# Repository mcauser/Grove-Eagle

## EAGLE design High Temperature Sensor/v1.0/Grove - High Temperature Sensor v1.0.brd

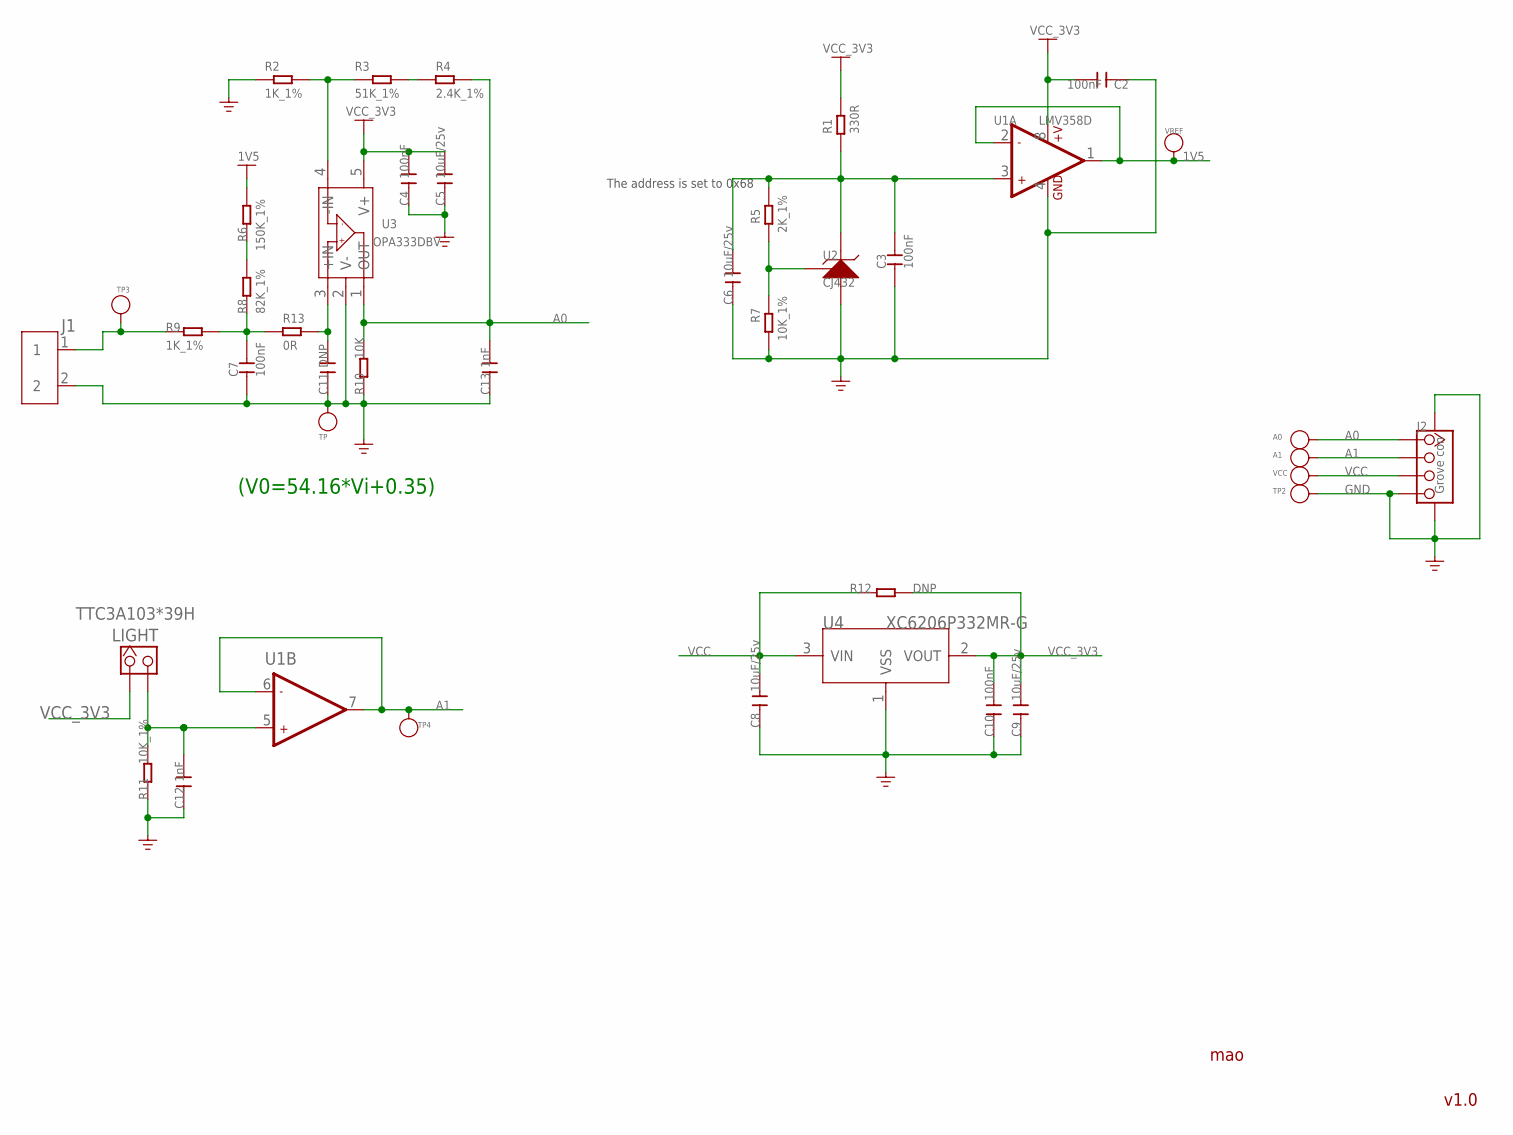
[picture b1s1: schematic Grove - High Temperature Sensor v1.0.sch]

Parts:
A0, A1: TP3; TP_4545
C2, C3, C4, C7, C10: 100nF; C0603
C5, C6, C8, C9: 10uF/25v; C0805
C11: DNP; C0603
C12, C13: 1nF; C0603
J1: SCREW-TERMINAL-2P'3.5'; 2P-3.5
J2: Grove con; 4P-SMD-2.0
LIGHT: TTC3A103*39H; CK_1*2
R1: 330R; R0603
R2, R9: 1K_1%; R0603
R3: 51K_1%; R0603
R4: 2.4K_1%; R0603
R5: 2K_1%; R0603
R6: 150K_1%; R0603
R7, R11: 10K_1%; R0603
R8: 82K_1%; R0603
R10: 10K; R0603
R12: DNP; R0603
R13: 0R; R0603
TP, TP2, TP3, TP4: PAD-TEST-POINT'4545'; TP_4545
U1: LMV358D; SO08
U2: CJ432; SOT23
U3: OPA333DBV; SOT23-5
U4: XC6206P332MR-G; SOT23
VCC: TP2; TP_4545
VREF: TP4; TP_4545

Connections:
1V5: R6.2, U1.1 (OUT1), U1.2 (-IN1), VREF.T
A0: A0.T, C13.2, J2.1, R4.1, R10.2, U3.1 (OUT)
A1: A1.T, J2.2, TP4.T, U1.6 (-IN2), U1.7 (OUT2)
GND: C2.1, C3.1, C4.1, C5.1, C6.1, C7.1, C8.1, C9.1, C10.1, C11.1, C12.1, C13.1, J1.2, J2.4, J2.SS1, J2.SS2, R2.2, R7.2, R10.1, R11.1, TP.T, TP2.T, U1.4 (GND), U2.3 (A), U3.2 (V-), U4.1 (VSS)
unnamed: C7.2, R8.1, R9.2, R13.2
unnamed: R2.1, R3.2, U3.4 (-IN)
unnamed: J1.1, R9.1, TP3.T
unnamed: R3.1, R4.2
unnamed: C12.2, LIGHT.2, R11.2, U1.5 (+IN2)
unnamed: R6.1, R8.2
unnamed: C11.2, R13.1, U3.3 (+IN)
unnamed: R5.2, R7.1, U2.1 (R)
VCC: C8.2, J2.3, R12.1, U4.3 (VIN), VCC.T
VCC_3V3: C2.2, C4.2, C5.2, C9.2, C10.2, LIGHT.1, R1.1, R12.2, U1.8 (+V), U3.5 (V+), U4.2 (VOUT)
VREF: C3.2, C6.2, R1.2, R5.1, U1.3 (+IN1), U2.2 (K)

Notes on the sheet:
mao
v1.0
The address is set to 0x68
(V0=54.16*Vi+0.35)

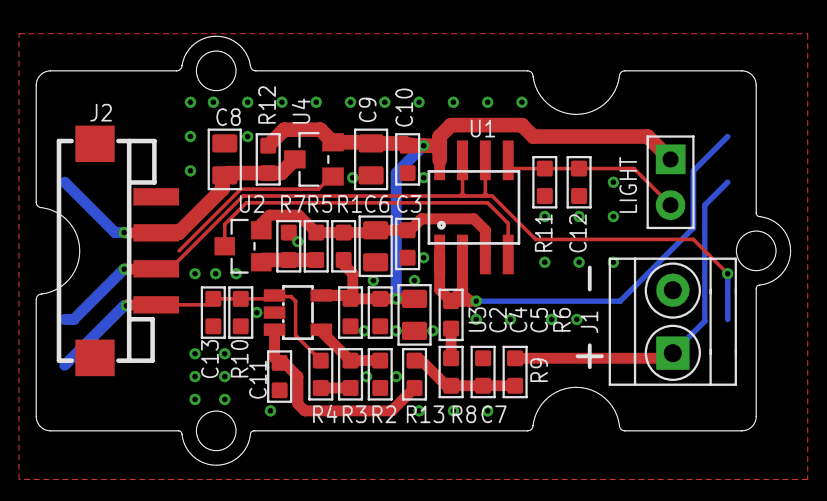
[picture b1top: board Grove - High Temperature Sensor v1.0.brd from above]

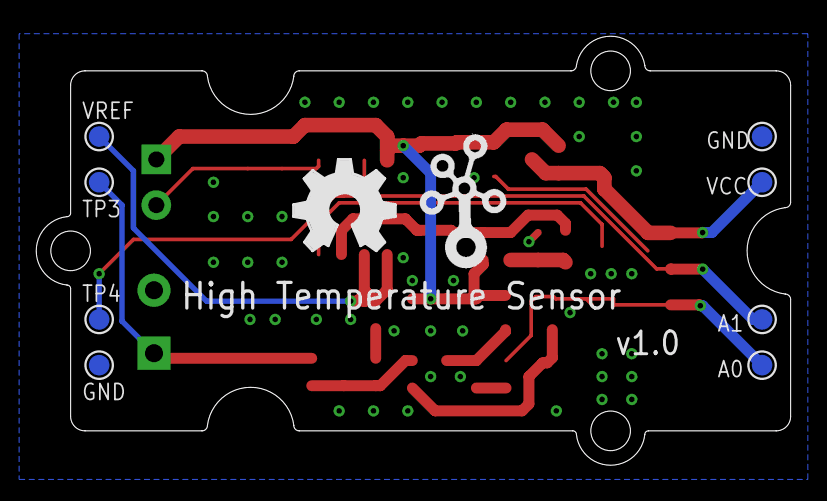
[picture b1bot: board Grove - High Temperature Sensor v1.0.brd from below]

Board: 2 copper layers, 41.9 x 23.8 mm, 43 parts (10 on the bottom side), 15 nets.

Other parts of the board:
U$9: GROVE-2CONNECTOR-SMD
U$11: TWIGLOGO
U$12: OSHW_FILLX200_NOTEXT

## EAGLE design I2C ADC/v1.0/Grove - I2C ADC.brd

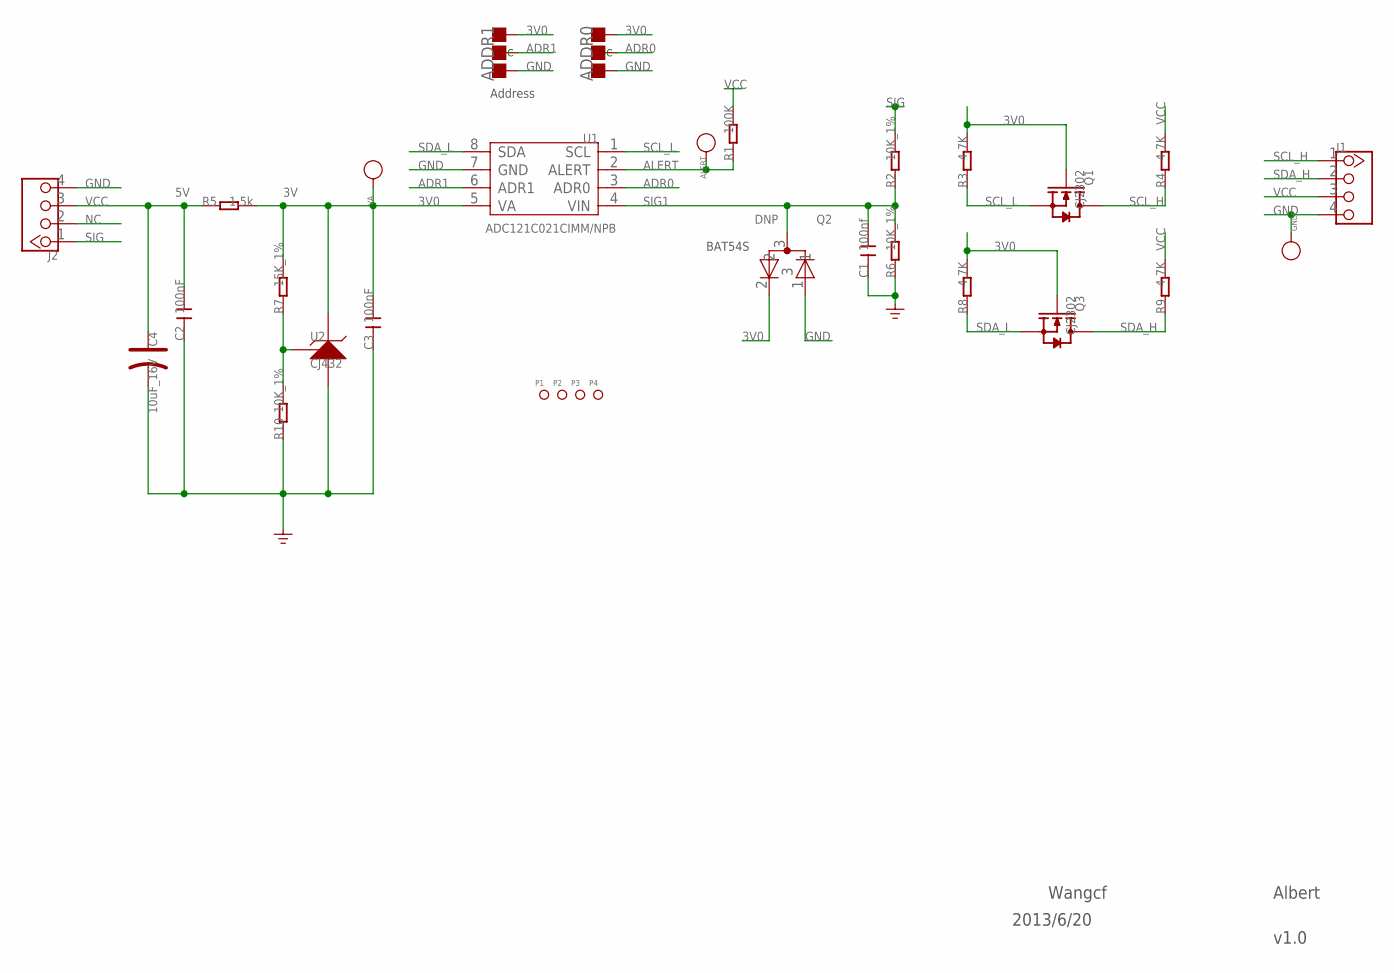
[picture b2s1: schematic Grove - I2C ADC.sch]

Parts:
ADDR0, ADDR1: DNP; 3P-SMD-4.1X1.5
ALERT: DNP; TP_3535; PARTNO DNP
C1: 100nf; C0603
C2, C3: 100nF; C0603
C4: 10uF_16V; AVX-A
GND: DNP; TP_3535
J1, J2: TWIG-4P-2.0-2.0; 4P-2.0
P1, P2, P3, P4: PAD-MARK; ROUND-MARK-1.0
Q1, Q3: CJ2302; SOT23
Q2: DNP; SOT23
R1: 100K; R0603
R2, R6, R10: 10K_1%; R0603
R3, R4, R8, R9: 4.7K; R0603
R5: 1.5k; R0603
R7: 15K_1%; R0603
U1: ADC121C021CIMM/NPB; MSOP8
U2: CJ432; SOT23
VA: DNP; TP_3535

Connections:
3V0: ADDR0.11 (R), ADDR1.11 (R), C3.2, Q1.1 (G), Q2.2, Q3.1 (G), R3.2, R5.2, R7.2, R8.2, U1.5 (VA), U2.2 (K), VA.T
ADR0: ADDR0.MM (C), U1.3 (ADR0)
ADR1: ADDR1.MM (C), U1.6 (ADR1)
ALERT: ALERT.T, R1.1, U1.2 (ALERT)
GND: ADDR0.00 (L), ADDR1.00 (L), C1.1, C2.1, C3.1, C4.-, GND.T, J1.4, J2.4, Q2.1, R6.1, R10.1, U1.7 (GND), U2.3 (A)
unnamed: R7.1, R10.2, U2.1 (R)
NC: J2.2
SCL_H: J1.1, Q1.3 (D), R4.1
SCL_L: Q1.2 (S), R3.1, U1.1 (SCL)
SDA_H: J1.2, Q3.3 (D), R9.1
SDA_L: Q3.2 (S), R8.1, U1.8 (SDA)
SIG: J2.1, R2.2
SIG1: C1.2, Q2.3, R2.1, R6.2, U1.4 (VIN)
VCC: C2.2, C4.+, J1.3, J2.3, R4.2, R5.1, R9.2

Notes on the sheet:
Address
BAT54S
Wangcf
Albert
2013/6/20
v1.0

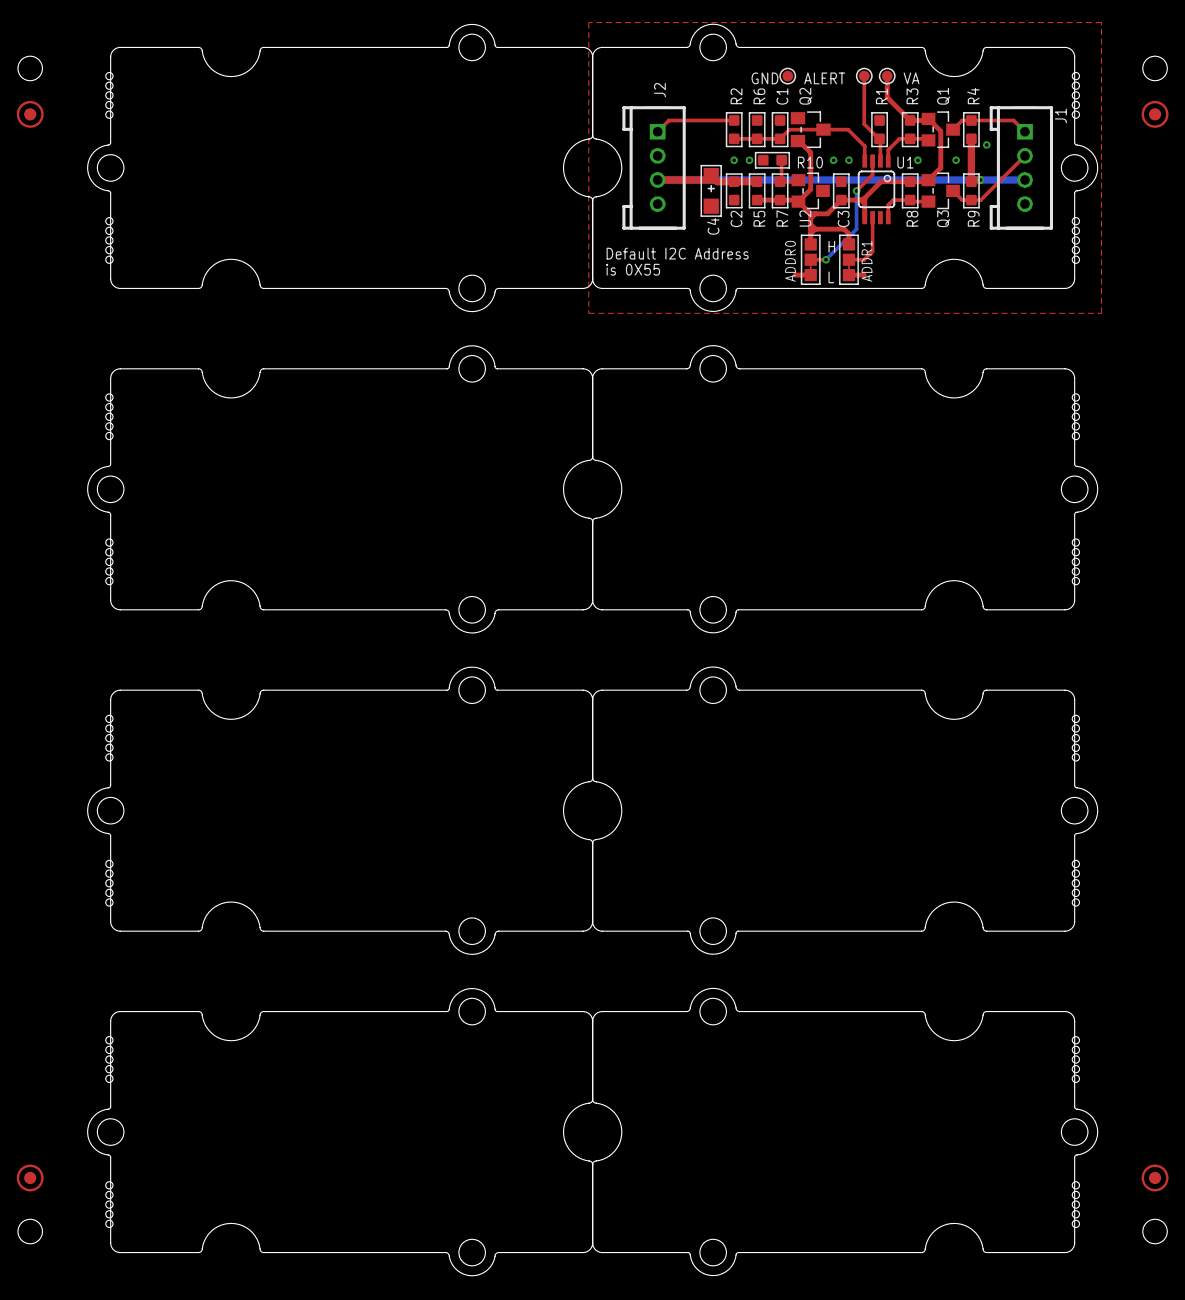
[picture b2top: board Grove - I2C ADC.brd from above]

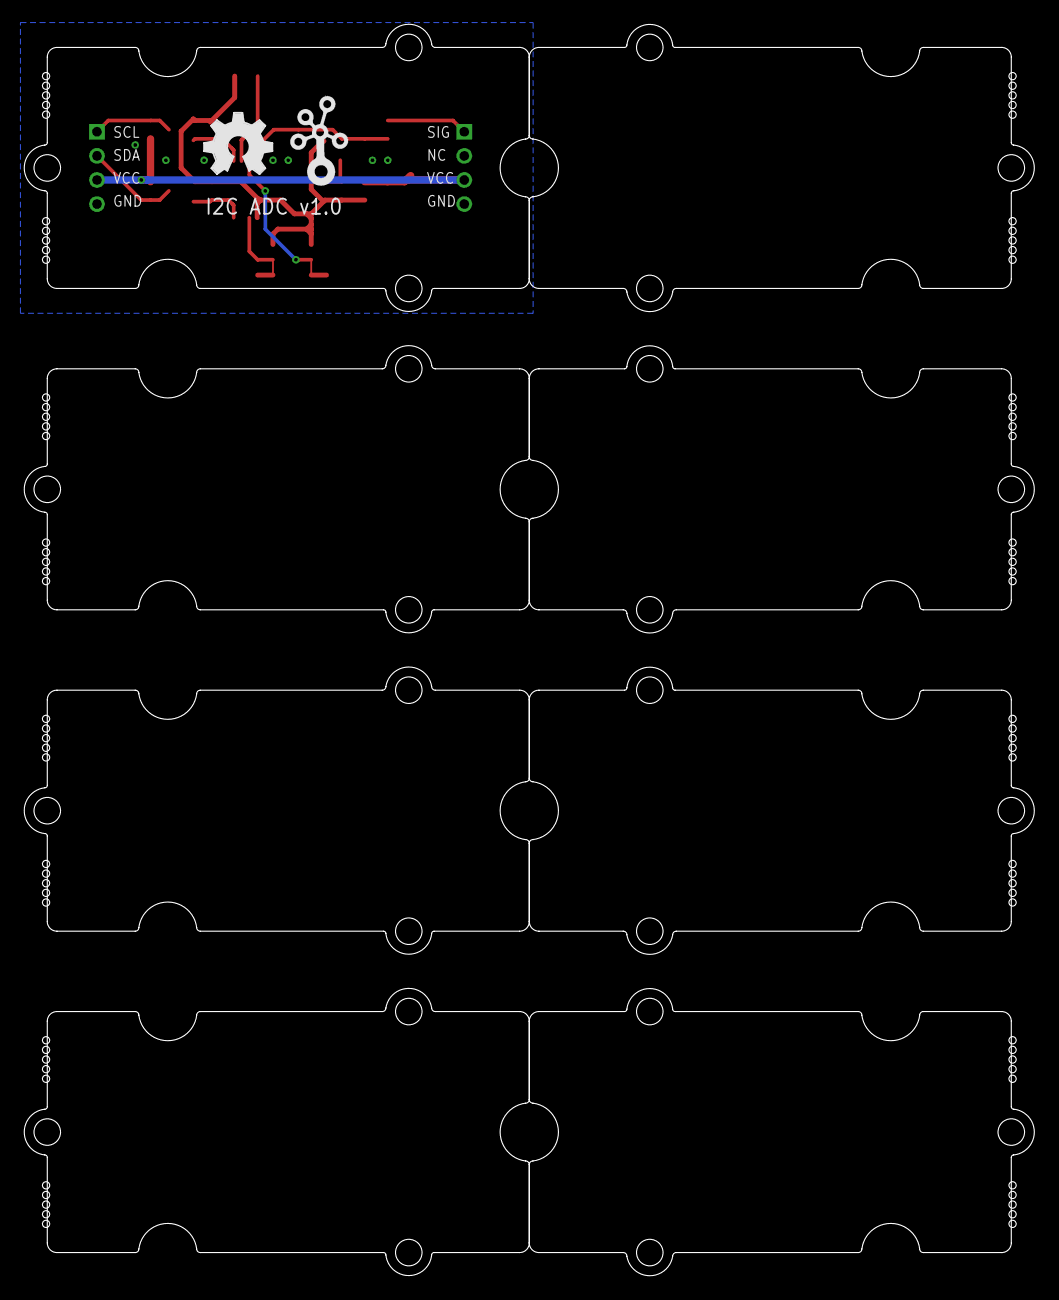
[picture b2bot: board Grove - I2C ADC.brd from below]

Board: 2 copper layers, 83.8 x 103.9 mm, 40 parts (2 on the bottom side), 13 nets.

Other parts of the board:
U$4, U$7, U$8, U$9, U$10, U$11, U$12, U$13: 2U-DIM-W/DRILL
U$5: OSHW_FILLX200_NOTEXT
U$6: TWIGLOGO

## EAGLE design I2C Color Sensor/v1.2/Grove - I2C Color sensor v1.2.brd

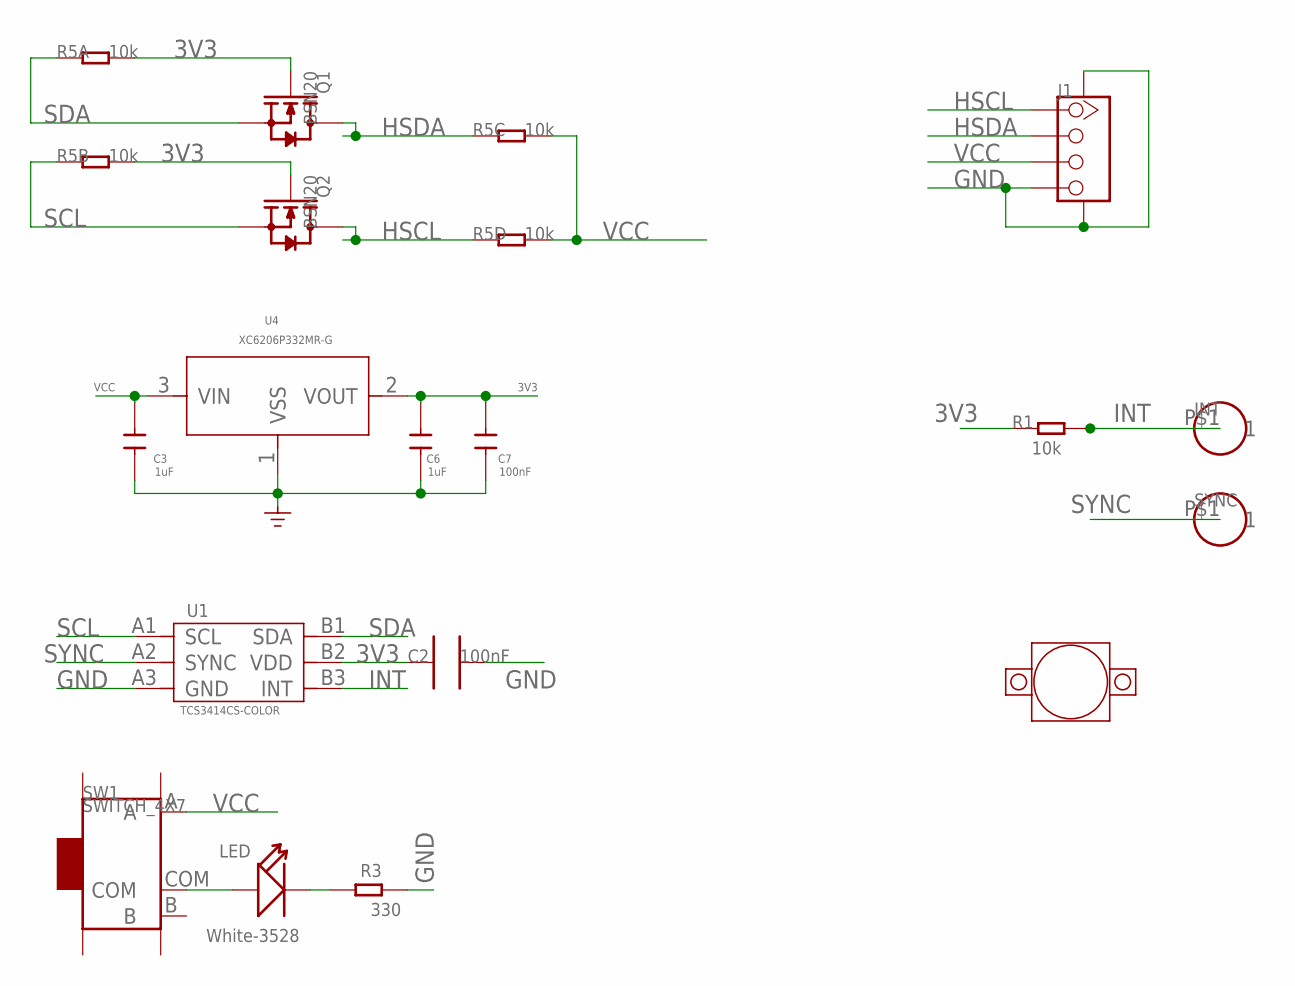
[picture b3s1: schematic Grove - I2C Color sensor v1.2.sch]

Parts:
C2: 100nF; 0603_S
C3, C6: 1uF; C0603
C7: 100nF; C0603
INT: CK_1X132; CK_1X1
J1: TWIG-4P-2.0-SMD-FEMALE-REINFORCE'DD'; 4P-SMD-2.0
LED: White-3528; LED1210
Q1, Q2: BSN20; SOT23
R1: 10k; 0603
R3: 330; 0603
R5: 10k; R1206-8
SW1: SWITCH_4X7; 4*8_SW
SYNC: CK_1X132; CK_1X1
U1: TCS3414CS-COLOR; TCS3414CS
U3: LENS_HOOD
U4: XC6206P332MR-G; SOT23

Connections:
3V3: C2.1, C6.2, C7.2, Q1.1 (G), Q2.1 (G), R1.1, R5.7 (2), R5.8 (2), U1.B2 (VDD), U4.2 (VOUT)
GND: C2.2, C3.1, C6.1, C7.1, J1.4, J1.SS1, J1.SS2, R3.1, U1.A3 (GND), U4.1 (VSS)
HSCL: J1.1, Q2.3 (D), R5.4 (1)
HSDA: J1.2, Q1.3 (D), R5.3 (1)
INT: INT.P$1, R1.2, U1.B3 (INT)
unnamed: LED.1 (+), SW1.COM
unnamed: LED.2 (-), R3.2
SCL: Q2.2 (S), R5.2 (1), U1.A1 (SCL)
SDA: Q1.2 (S), R5.1, U1.B1 (SDA)
SYNC: SYNC.P$1, U1.A2 (SYNC)
VCC: C3.2, J1.3, R5.5 (2), R5.6 (2), SW1.A, U4.3 (VIN)

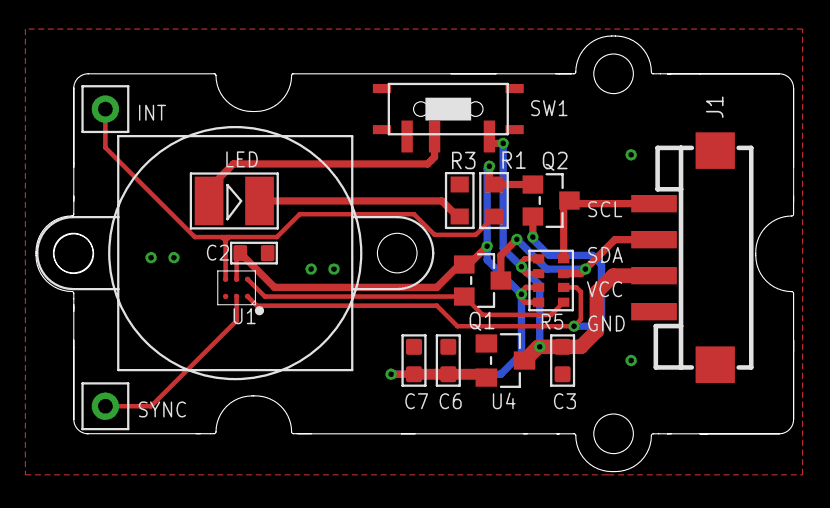
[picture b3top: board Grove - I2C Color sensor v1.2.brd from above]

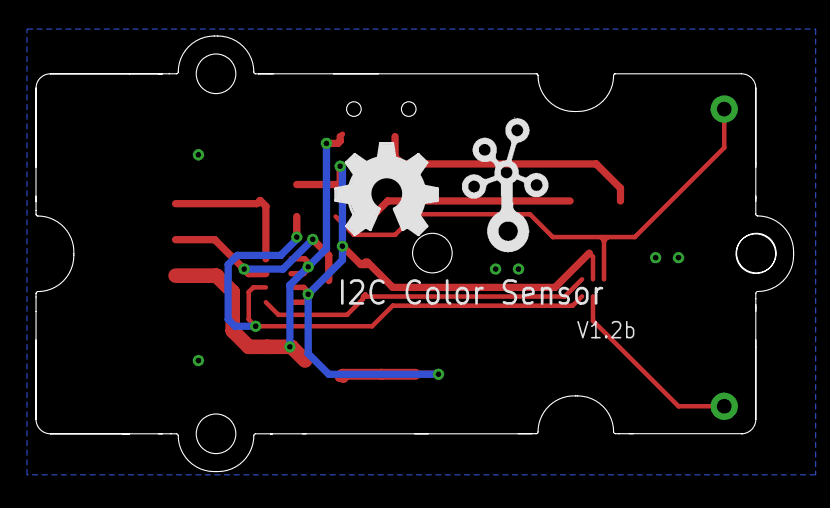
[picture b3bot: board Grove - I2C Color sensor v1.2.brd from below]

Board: 2 copper layers, 42.1 x 24.2 mm, 20 parts (2 on the bottom side), 11 nets.

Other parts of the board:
U$1: TWIGLOGO
U$2: 2U-DIM-W/-DRILL
U$3: OSHW_FILLX200_NOTEXT

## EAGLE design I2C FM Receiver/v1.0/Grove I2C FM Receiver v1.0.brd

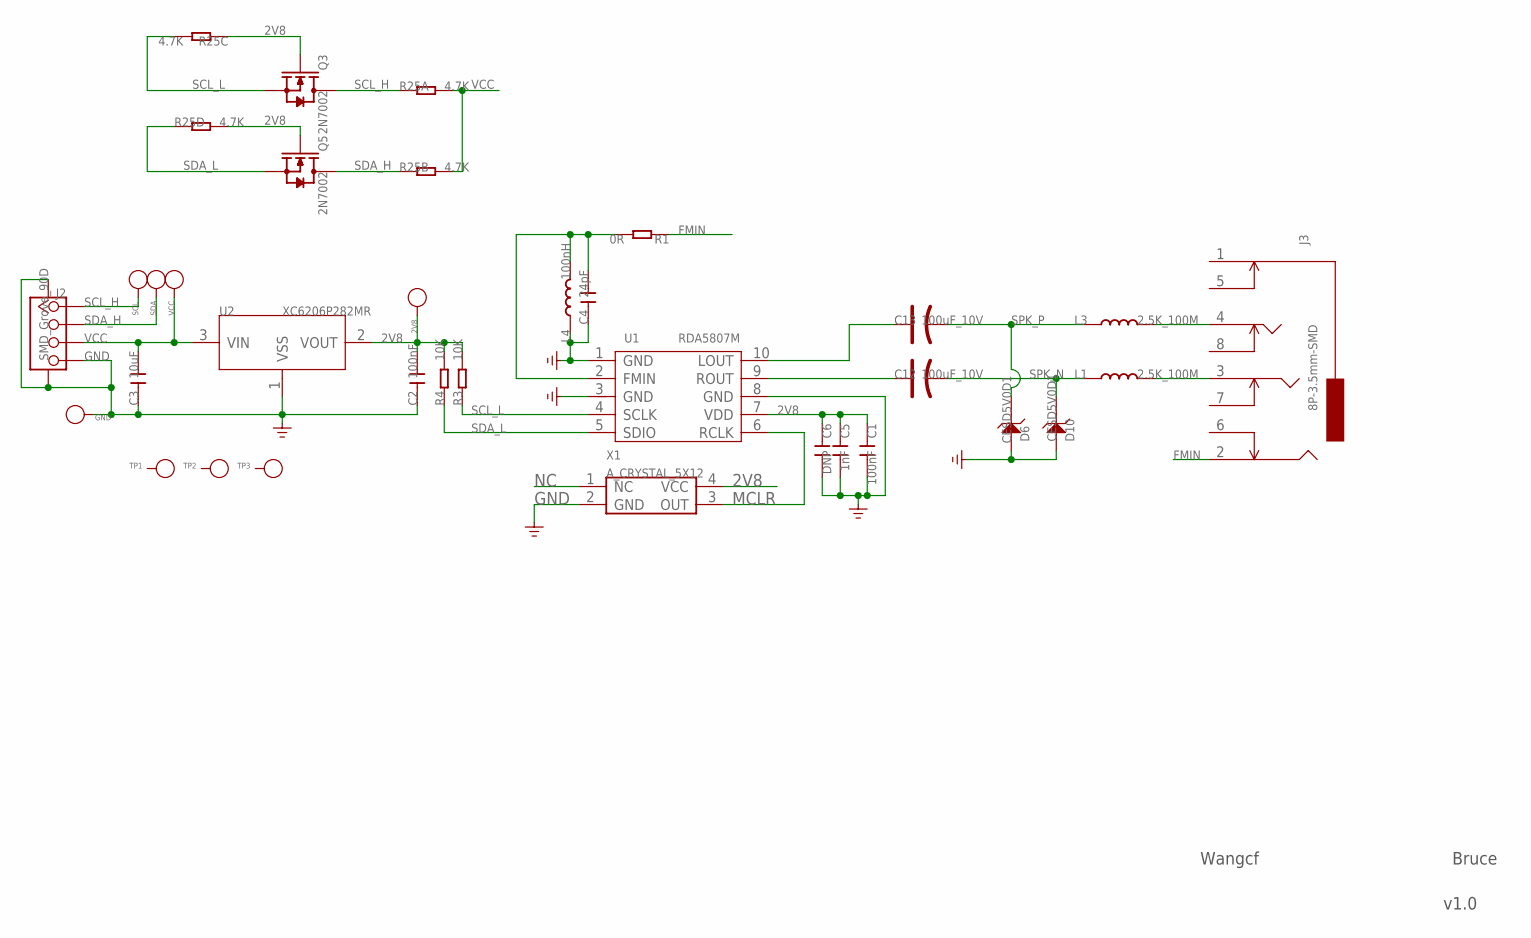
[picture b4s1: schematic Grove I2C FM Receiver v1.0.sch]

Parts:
2V8: PAD-TEST-POINT'4545'; TP_4545
C1, C2: 100nF; C0603
C3: 10uF; C0805
C4: 24pF; C0603
C5: 1nF; C0603
C6: DNP; C0603
C12, C13: 100uF_10V; AVX-B
D6, D10: CESD5V0D1; SOD123-2.7X1.6
GND: PAD-TEST-POINT'4545'; TP_4545
J2: SMD_Grove_90D; 4P-SMD-2.0
J3: 8P-3.5mm-SMD; 8P-3.5-SMD
L1, L3: 2.5K_100M; L0603
L4: 100nH; L0603
Q3, Q5: 2N7002; SOT23
R1: 0R; R0603
R3, R4: 10K; R0603
R25: 4.7K; 1206-8-3.3X2.4
SCL: PAD-TEST-POINT'4545'; TP_4545
SDA: PAD-TEST-POINT'4545'; TP_4545
TP1, TP2, TP3: PAD-TEST-POINT'4545'; TP_4545
U1: RDA5807M; MSOP10
U2: XC6206P282MR; SOT23
VCC: PAD-TEST-POINT'4545'; TP_4545
X1: A_CRYSTAL_5X12; 4P_5X12

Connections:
2V8: 2V8.T, C1.1, C2.2, C5.1, C6.1, Q3.1 (G), Q5.1 (G), R3.2, R4.2, R25.3 (1), R25.5 (2), U1.7 (VDD), U2.2 (VOUT), X1.4 (VCC)
FMIN: J3.2, R1.1
FMIN1: C4.2, L4.2, R1.2, U1.2 (FMIN)
GND: C1.2, C2.1, C3.1, C4.1, C5.2, C6.2, D6.1, D10.1, GND.T, J2.4, J2.SS1, J2.SS2, L4.1, U1.1 (GND), U1.3 (GND), U1.8 (GND), U2.1 (VSS), X1.2 (GND)
MCLR: U1.6 (RCLK), X1.3 (OUT)
unnamed: C12.+, U1.9 (ROUT)
unnamed: C13.+, U1.10 (LOUT)
unnamed: J3.4, L3.2
unnamed: J3.3, L1.2
NC: X1.1 (NC)
SCL_H: J2.1, Q3.3 (D), R25.1, SCL.T
SCL_L: Q3.2 (S), R3.1, R25.6 (2), U1.4 (SCLK)
SDA_H: J2.2, Q5.3 (D), R25.2 (1), SDA.T
SDA_L: Q5.2 (S), R4.1, R25.4 (1), U1.5 (SDIO)
SPK_N: C12.-, D10.2, L1.1
SPK_P: C13.-, D6.2, L3.1
VCC: C3.2, J2.3, R25.7 (2), R25.8 (2), U2.3 (VIN), VCC.T

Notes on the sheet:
Wangcf
Bruce
v1.0

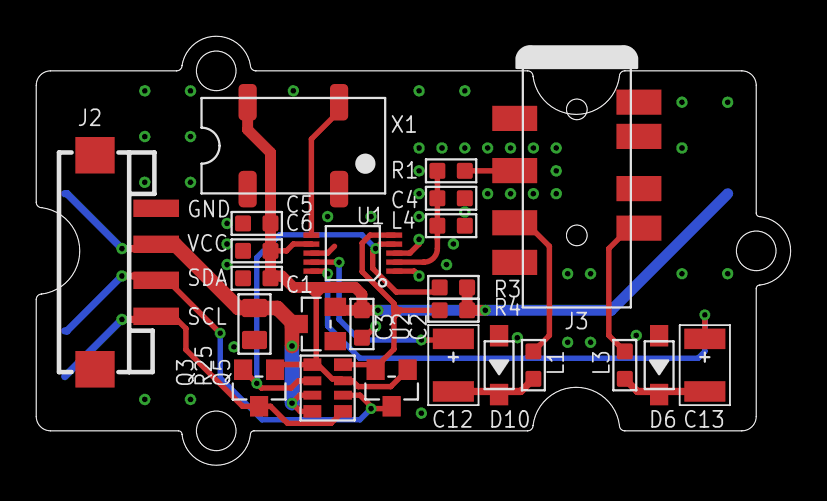
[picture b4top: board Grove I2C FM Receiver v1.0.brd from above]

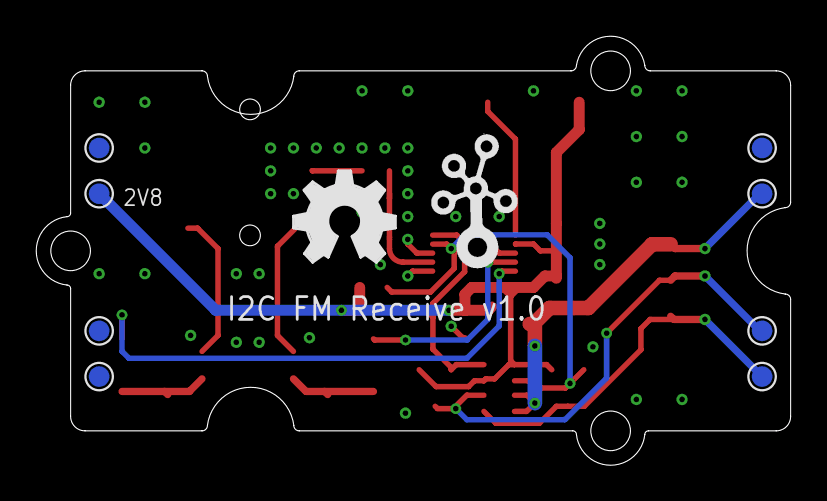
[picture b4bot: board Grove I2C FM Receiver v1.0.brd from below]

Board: 2 copper layers, 41.9 x 23.8 mm, 35 parts (10 on the bottom side), 16 nets.

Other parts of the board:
U$6: GROVE-TEST-PLATFORM
U$7: OSHW_FILLX200_NOTEXT
U$11: TWIGLOGO

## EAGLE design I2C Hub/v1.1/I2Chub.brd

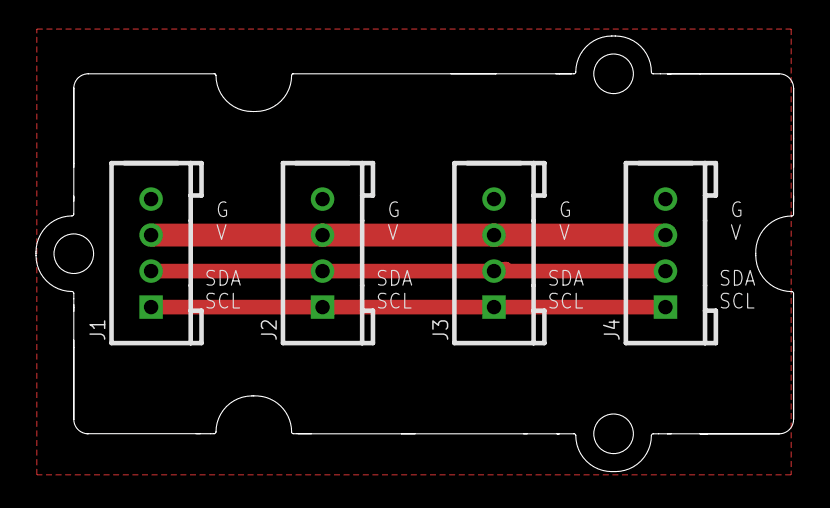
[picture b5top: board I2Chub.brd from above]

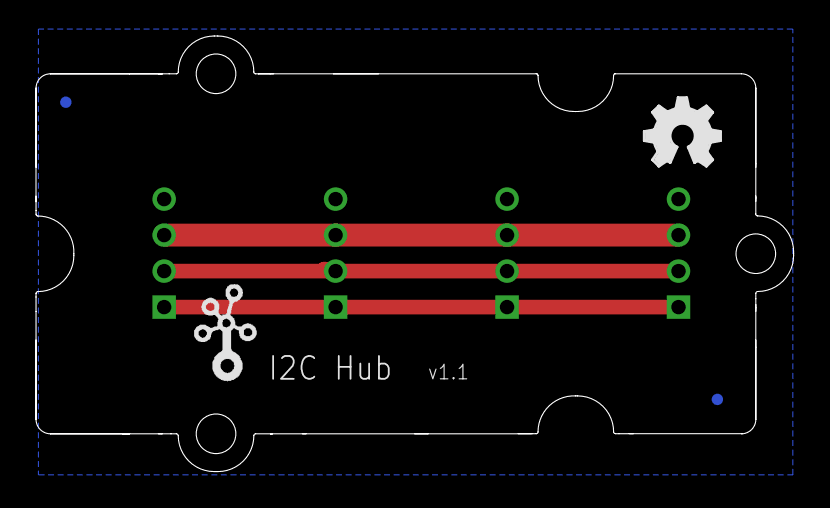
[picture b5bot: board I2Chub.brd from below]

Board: 2 copper layers, 42.1 x 24.2 mm, 9 parts (4 on the bottom side), 4 nets.

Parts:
J1, J2, J3, J4: TWIG-2.0-DIP; 2.0_1X4
LOGO3: LOGO-OSHW-FILLX0150-NT; OSHW_FILLX150_NOTEXT
MARK1, MARK2: PAD-MARK; MARK
TWIG1: TWIG-W/O-VIAU2; U2N
U$1: TWIGLOGOTWIGLOGO_SMALL; TWIGLOGO_SMALL

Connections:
GND: J1.4, J2.4, J3.4, J4.4
SCL: J1.1, J2.1, J3.1, J4.1
SDA: J1.2, J2.2, J3.2, J4.2
VCC: J1.3, J2.3, J3.3, J4.3
